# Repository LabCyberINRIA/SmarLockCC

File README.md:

Printed Circuit Board designed with Kicad to control an electrical lock.
It has a microcontroller (ESP32-C3) capable of bluetooth, WiFi and USB, a connector for a RFID reader board based on NXP MFRC522 chip, a servomotor connector and RGB LED.

To program the board using Arduino IDE, you need to add the ESP32 support https://docs.espressif.com/projects/arduino-esp32/en/latest/installing.html

Connect your board and select the "Adafruit QT Py ESP32-C3" board, and the port that should appear. The first time or if the port does not appear, you need to put manually your board in download mode : push the boot button, power or reset the board, then release the boot button.

You should be able to flash an example to the board.

For the LED, you can use the Adafruit NeoPixel library, test it with RGBWstrandtest example configured with the LED_PIN set to 2 and LED_COUNT set to 1

For the RFID board, the RST_PIN is 7, SS_PIN is 10, and SPI.begin(4, 5, 6, 10).

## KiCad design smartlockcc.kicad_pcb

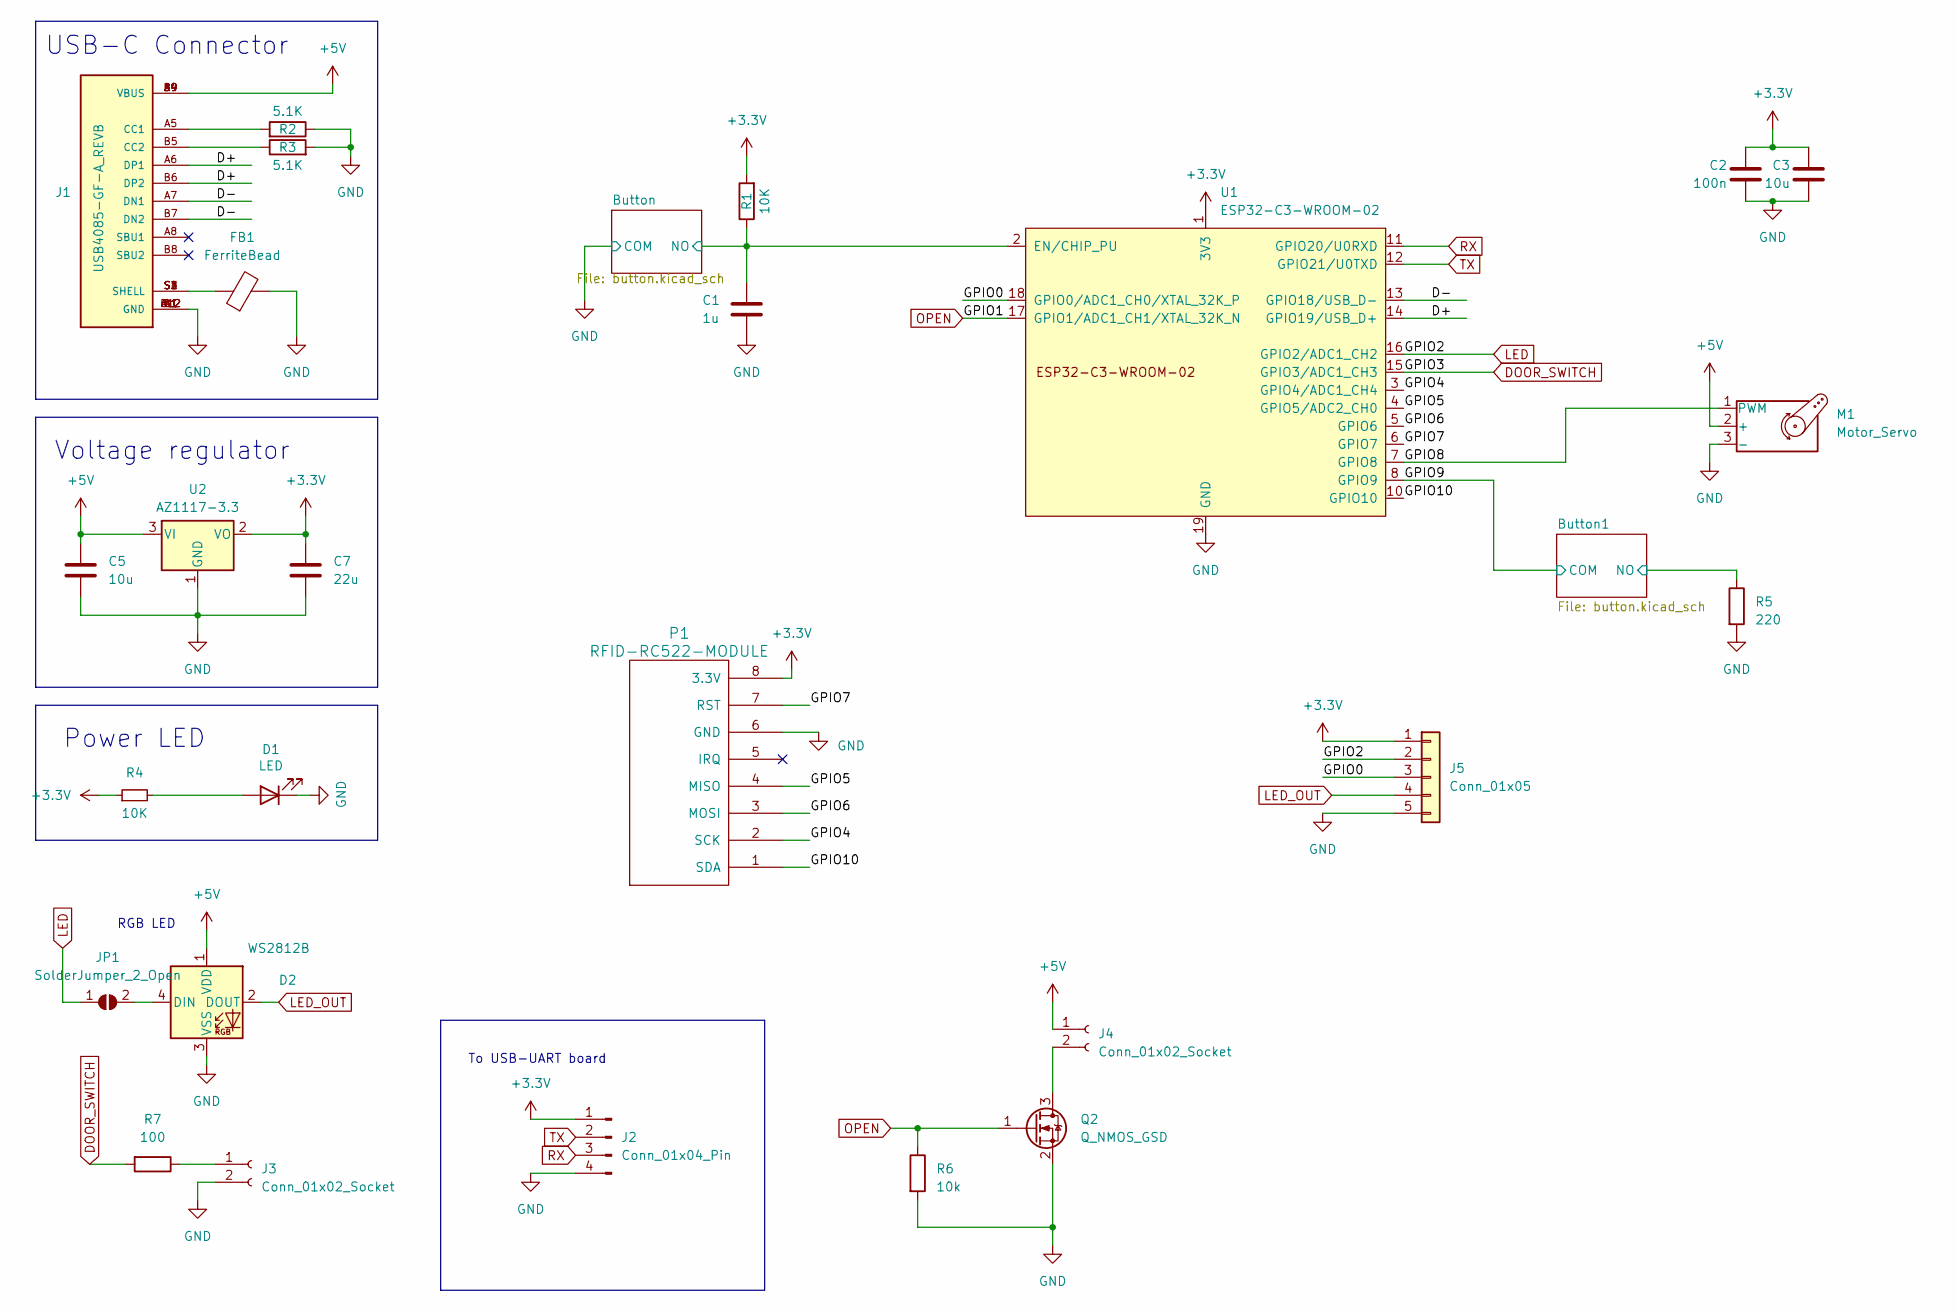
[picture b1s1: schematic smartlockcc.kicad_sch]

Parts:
C1: 1u; C_0805_2012Metric_Pad1.18x1.45mm_HandSolder
C2: 100n; C_0805_2012Metric_Pad1.18x1.45mm_HandSolder
C3, C5: 10u; C_0805_2012Metric_Pad1.18x1.45mm_HandSolder
C7: 22u; C_0805_2012Metric_Pad1.18x1.45mm_HandSolder
D1: LED; D_0805_2012Metric_Pad1.15x1.40mm_HandSolder; Manufacturer_Part_Number VSMB1940X01; Mouser Part Number 782-VSMB1940X01
D2: WS2812B; LED_WS2812B_PLCC4_5.0x5.0mm_P3.2mm
FB1: FerriteBead; R_0805_2012Metric_Pad1.20x1.40mm_HandSolder
J1: USB4085-GF-A_REVB; GCT_USB4085-GF-A_REVB; PARTREV B
J2: Conn_01x04_Pin; PinHeader_1x04_P2.54mm_Vertical
J3, J4: Conn_01x02_Socket; PinSocket_1x02_P2.54mm_Horizontal
J5: Conn_01x05; PinHeader_1x05_P2.00mm_Vertical
JP1: SolderJumper_2_Open; SolderJumper-2_P1.3mm_Open_TrianglePad1.0x1.5mm
M1: Motor_Servo; PinHeader_1x03_P2.54mm_Horizontal
P1: RFID-RC522-MODULE; PinSocket_1x08_P2.54mm_Vertical
Q2: Q_NMOS_GSD; SOT-23-3
R1: 10K; R_0805_2012Metric_Pad1.20x1.40mm_HandSolder
R2, R3: 5.1K; R_0805_2012Metric_Pad1.20x1.40mm_HandSolder
R4: 10K; R_0805_2012Metric_Pad1.20x1.40mm_HandSolder; MPN DNP
R5: 220; R_0805_2012Metric_Pad1.20x1.40mm_HandSolder
R6: 10k; R_0805_2012Metric_Pad1.20x1.40mm_HandSolder
R7: 100; R_0805_2012Metric_Pad1.20x1.40mm_HandSolder
U1: ESP32-C3-WROOM-02
U2: AZ1117-3.3; SOT-89-3_Handsoldering

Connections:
+3.3V: C2.1, C3.1, C7.1, J2.1, J5.1, P1.8 (3.3V), R1.2, R4.1, U1.1 (3V3), U2.2 (VO)
+5V: C5.1, D2.1 (VDD), J1.A4 (VBUS), J1.A9 (VBUS), J1.B4 (VBUS), J1.B9 (VBUS), J4.1, M1.2 (+), U2.3 (VI)
/Button1/NO: R5.1; also elsewhere on the board
/Button/NO: C1.1, R1.1, U1.2 (EN/CHIP_PU); also elsewhere on the board
/D+: J1.A6 (DP1), J1.B6 (DP2), U1.14 (GPIO19/USB_D+)
/D-: J1.A7 (DN1), J1.B7 (DN2), U1.13 (GPIO18/USB_D-)
/GPIO0: J5.3, U1.18 (GPIO0/ADC1_CH0/XTAL_32K_P)
/GPIO4: P1.2 (SCK), U1.3 (GPIO4/ADC1_CH4)
/GPIO5: P1.4 (MISO), U1.4 (GPIO5/ADC2_CH0)
/GPIO6: P1.3 (MOSI), U1.5 (GPIO6)
/GPIO7: P1.7 (RST), U1.6 (GPIO7)
/GPIO8: M1.1 (PWM), U1.7 (GPIO8)
/GPIO9: U1.8 (GPIO9); also elsewhere on the board
/GPIO10: P1.1 (SDA), U1.10 (GPIO10)
DOOR_SWITCH: R7.2, U1.15 (GPIO3/ADC1_CH3)
GND: C1.2, C2.2, C3.2, C5.2, C7.2, D1.1 (K), D2.3 (VSS), FB1.2, J1.A1 (GND), J1.A12 (GND), J1.B1 (GND), J1.B12 (GND), J2.4, J3.2, J5.5, M1.3 (-), P1.6 (GND), Q2.2 (S), R2.1, R3.2, R5.2, R6.2, U1.9 (GND), U1.19 (GND), U2.1 (GND); also elsewhere on the board
LED: J5.2, JP1.1 (A), U1.16 (GPIO2/ADC1_CH2)
LED_OUT: D2.2 (DOUT), J5.4
unnamed: D1.2 (A), R4.2
unnamed: D2.4 (DIN), JP1.2 (B)
unnamed: FB1.1, J1.S1 (SHELL), J1.S2 (SHELL), J1.S3 (SHELL), J1.S4 (SHELL)
unnamed: J1.A5 (CC1), R2.2
unnamed: J1.B5 (CC2), R3.1
unnamed: J3.1, R7.1
unnamed: J4.2, Q2.3 (D)
OPEN: Q2.1 (G), R6.1, U1.17 (GPIO1/ADC1_CH1/XTAL_32K_N)
RX: J2.3, U1.11 (GPIO20/U0RXD)
TX: J2.2, U1.12 (GPIO21/U0TXD)

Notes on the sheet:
Voltage regulator
Power LED
RGB LED
To USB-UART board
USB-C Connector

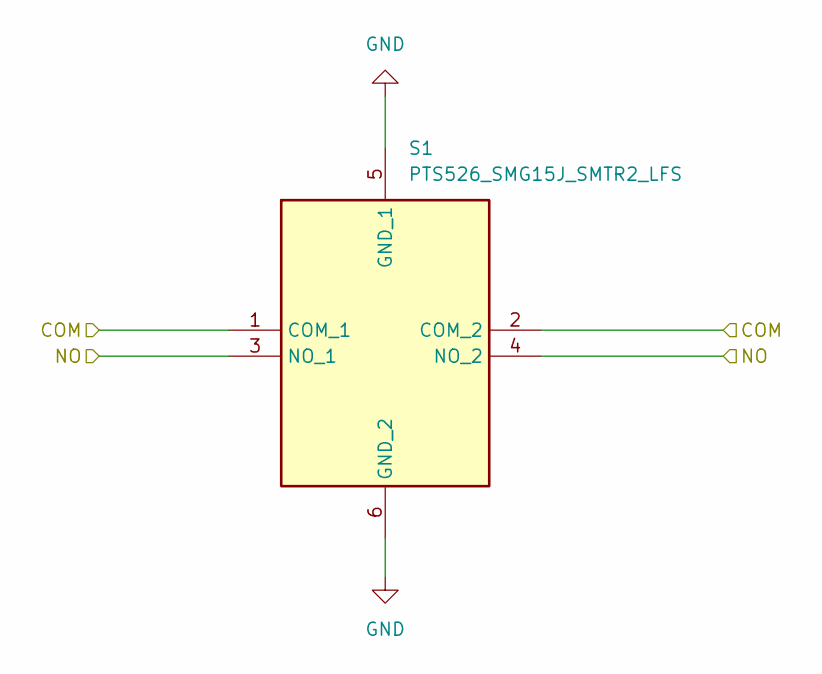
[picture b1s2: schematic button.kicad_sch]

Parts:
S1: PTS526_SMG15J_SMTR2_LFS; PTS526SMG15JSMTR2LFS; Manufacturer_Part_Number PTS526 SMG15J SMTR2 LFS; Mouser Part Number 611-TS526SMG15JSMR2L

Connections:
/Button/NO: S1.3 (NO_1), S1.4 (NO_2); also elsewhere on the board
GND: S1.1 (COM_1), S1.2 (COM_2), S1.5 (GND_1), S1.6 (GND_2); also elsewhere on the board

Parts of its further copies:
S2: PTS526_SMG15J_SMTR2_LFS; PTS526SMG15JSMTR2LFS; Manufacturer_Part_Number PTS526 SMG15J SMTR2 LFS; Mouser Part Number 611-TS526SMG15JSMR2L

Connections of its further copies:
/Button1/NO: S2.3 (NO_1), S2.4 (NO_2); also elsewhere on the board
/GPIO9: S2.1 (COM_1), S2.2 (COM_2); also elsewhere on the board
GND: S2.5 (GND_1), S2.6 (GND_2); also elsewhere on the board

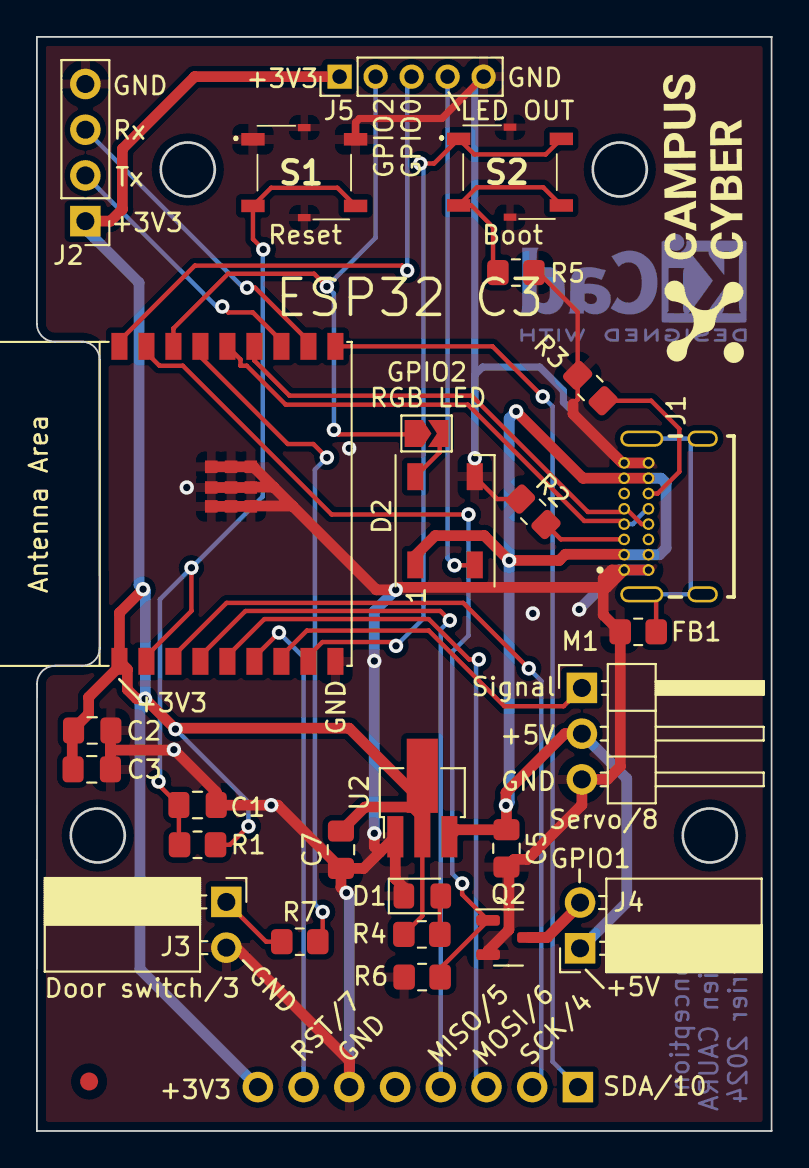
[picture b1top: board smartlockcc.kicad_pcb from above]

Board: 2 copper layers, 40.8 x 60.7 mm, 28 parts (1 on the bottom side), 28 nets.

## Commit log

2024-02-12 Files as sent to aisler, first batch
2024-03-07 Add README.md
2024-03-07 Test code added
2024-03-21 Cleanup and pictures added
2024-03-21 Links to pictures added in README.md
2024-05-07 Ajout identification simple (UID dans un tableau)
